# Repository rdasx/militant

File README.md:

Personal Vaporizer mod. Provides boost circuitry to run higher voltage as well as a built in USB charger. Will Probably be abandoned.

Files with "simple" in the name represent a subproject for a smaller, simpler, board that does away with the boost circuitry. Includes "in-situ" charging and a power mosfet for long switch life.

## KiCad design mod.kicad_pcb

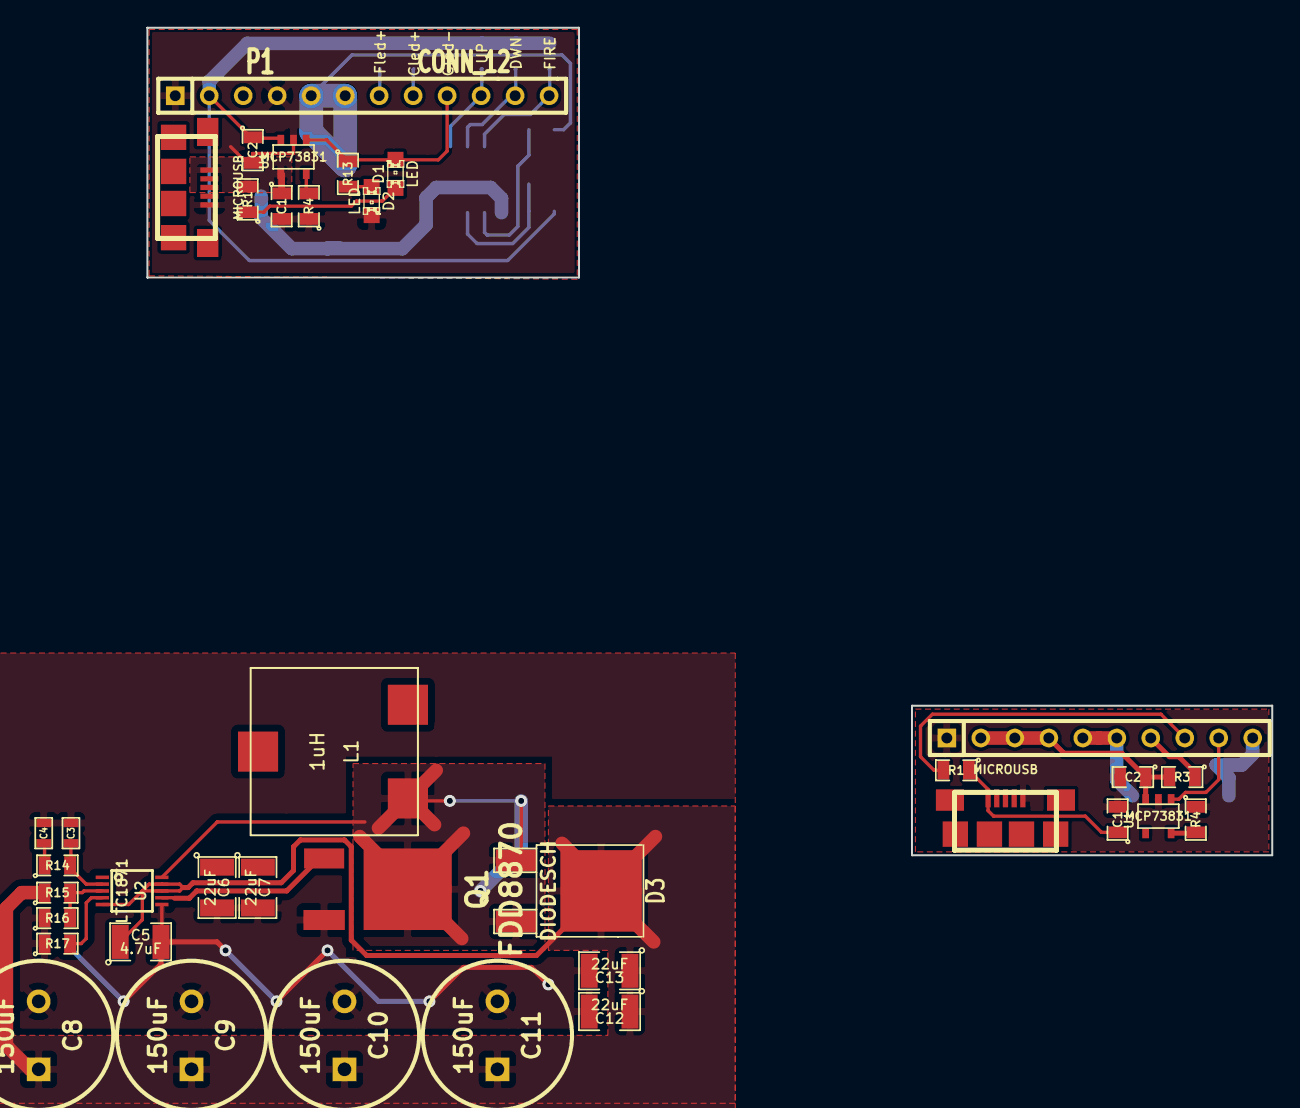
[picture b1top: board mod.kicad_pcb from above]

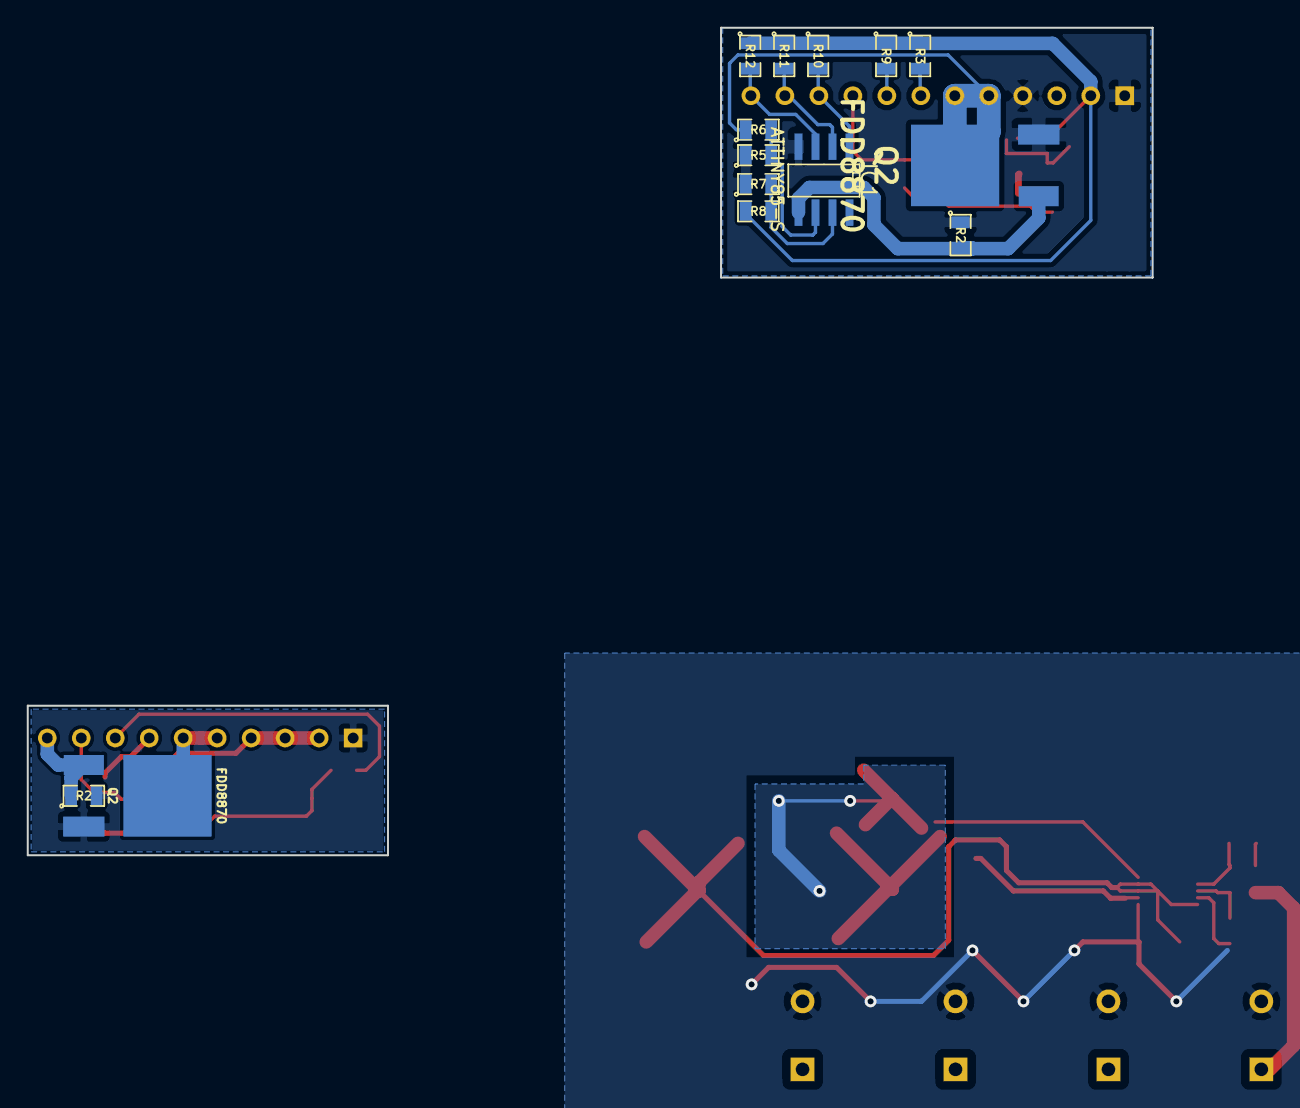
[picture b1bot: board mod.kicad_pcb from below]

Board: 2 copper layers, 51 parts (14 on the bottom side), 28 nets.

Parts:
C1, C1#2, C2, C2#2: 4.7uF; SM0805
C3: 47pF; SM0603
C4: 6800pF; SM0603
C5: 4.7uF; SM1210
C6, C7, C12, C13: 22uF; SM1210
C8, C9, C10, C11: 150uF; C2V10
D1, D2: LED; LED-0805
D3: DIODESCH; DPAK2_Schottky
IC1: ATTINY85-S; SO8(N)_MAXIC
J1, J1#2: MICROUSB; USBmicro
L1: 1uH; CEP125
P1: CONN_12; SIL-12
P1#2: CONN_10; SIL-10
Q1, Q2, Q2#2: FDD8870; TO-252_Mosfet
R1, R13: 1K; SM0805
R1#2, R3, R3#2, R5, R6, R7, R8, R9, R10, R11, R12: 330; SM0805
R2, R2#2: 10K; SM0805
R4, R4#2: 2K; SM0805
R14: 22K; SM0805
R15: 47K; SM0805
R16: 12.1K; SM0805
R17: 80.6K; SM0805
U1, U1#2: MCP73831; SOT23-5
U2: LTC1871; MSOP10-0.5

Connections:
/Atomizer+: C2#2.1, P1#2.2, P1#2.3, P1#2.4, R3#2.2, U1#2.3
/Atomizer-: P1.5, P1.6, P1#2.5, P1#2.6, Q2.D, Q2#2.D, R6.1
/Boost/Vout: C5.1, C8.1, C9.1, C10.1, C11.1, C12.1, C13.1, D3.2, P1.3, R15.1, U2.5, U2.8, U2.9
/ChargeLED+: P1.8, R9.2
/DWN-MCU: IC1.2, P1.11, R11.2
/FIRE-MCU: IC1.3, P1.12, R12.2
/FireLED+: P1.7, P1#2.7, R3.2, R3#2.1
/MCP73831 Charger/ChargeLED-: D1.2, P1.9, R13.1, U1.1
/MCP73831 Charger/Vbat: C2.1, C6.1, C7.1, IC1.8, L1.1, P1.2, R3.1, R8.2, R9.1, R10.1, R11.1, R12.1, U1.3, U2.1
/MCP73831 Charger/Vcharge: C1.1, J1.1, R1.2, U1.4
/Switch-: P1#2.10, Q2#2.G, R2#2.1
/UP-MCU: IC1.1, P1.10, R10.2
/chgLED+: P1#2.8, R1#2.2
/chgLED-: P1#2.9, U1#2.1
GND: C1.2, C1#2.2, C2.2, C2#2.2, C3.2, C4.2, C5.2, C6.2, C7.2, C8.2, C9.2, C10.2, C11.2, C12.2, C13.2, D2.2, IC1.4, J1.5, J1#2.5, P1.1, P1.4, P1#2.1, Q1.S, Q2.S, Q2#2.S, R2.1, R2#2.2, R4.1, R4#2.1, R5.1, R7.1, R16.1, R17.1, U1.2, U1#2.2, U2.6
unnamed: IC1.5, Q2.G, R2.2, R4#2.2, U1#2.5
unnamed: IC1.7, R7.2, R8.1
unnamed: IC1.6, R5.2, R6.2
unnamed: C1#2.1, J1#2.1, R1#2.1, U1#2.4
unnamed: D3.1, L1.2, Q1.D, U2.10
unnamed: Q1.G, U2.7
unnamed: R17.2, U2.4
unnamed: C4.1, R14.1
unnamed: R15.2, R16.2, U2.3
unnamed: C3.1, R14.2, U2.2
unnamed: D2.1, R13.2
unnamed: R4.2, U1.5
unnamed: D1.1, R1.1

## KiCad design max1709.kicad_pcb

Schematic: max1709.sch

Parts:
C1, C2, C4: 0.1uF; SM0805
C3: .22uF; SM0805
C5, C6, C7, C8: 150uF; C2V10
D1: DIODESCH; DPAK2
L1: 1uH
P1: CONN_6
R1: 2K; SM0805
RV1: POT
U1: MAX1709; tssop-28

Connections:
/FB: P1.3, RV1.2, U1.16
/ONA: P1.6, U1.1
/ONB: C1.1, P1.5, U1.28
/Vin: C7.1, C8.1, L1.1, P1.1
/Vout: C5.1, C6.1, D1.2 (K), P1.2, R1.2, RV1.1
GND: C1.2, C2.2, C3.2, C4.2, C5.2, C6.2, C7.2, C8.2, P1.4, RV1.3, U1.11, U1.18, U1.26
unnamed: C2.1, U1.12
unnamed: C4.1, R1.1, U1.15, U1.27
unnamed: C3.1, U1.13
unnamed: D1.1 (A), L1.2, U1.2

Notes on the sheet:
ONA ONB State 0 0 1 0 1 0 1 0 1 1 1 1
If MCU runs on Vout: Connect ONB to 270K pullup (to Vin), grounded push switch, and GPIO pin. Connect ONA to 270K pulldown (to GND), and GPIO Pin. Switch pushed, switch pulls ONB Down (REG ON), MCU Sees button push once running, MCU Pulls ONA High (REG locked ON), switch released, Switch pushed, MC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
If MCU does not run on Vout: Connect ONB to 270K pullup (to Vin) and grounded push switch or GPIO pin. Connect ONA to GND. Push switch or pull GPIO Pin low to enable (REG ON) Release switch or pull GPIO pin high to disable (REG OFF)
Vout = 1.24*(1+(R1/R2)) Where R1 is the Series Resistor and R2 is the pulldown

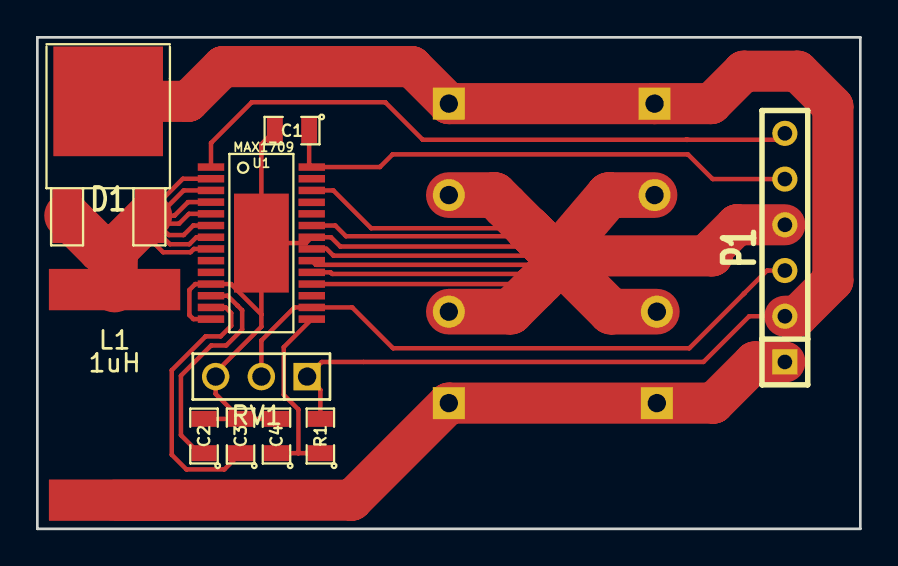
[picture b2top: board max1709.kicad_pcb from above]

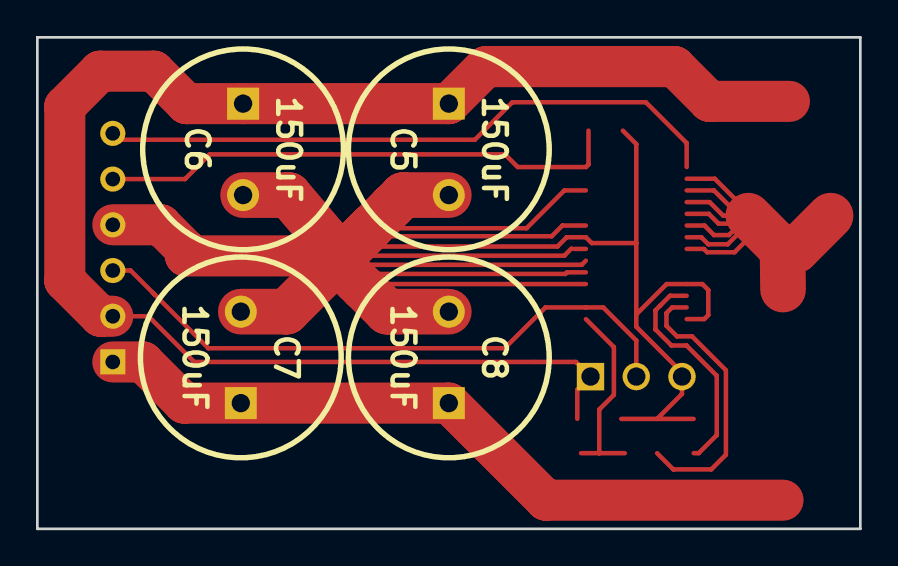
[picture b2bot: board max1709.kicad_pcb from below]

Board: 2 copper layers, 45.7 x 27.3 mm, 14 parts (4 on the bottom side), 10 nets.

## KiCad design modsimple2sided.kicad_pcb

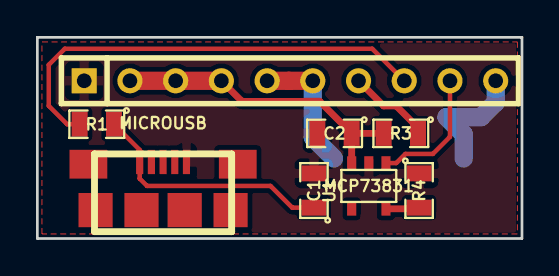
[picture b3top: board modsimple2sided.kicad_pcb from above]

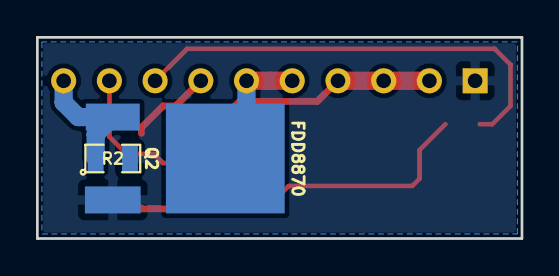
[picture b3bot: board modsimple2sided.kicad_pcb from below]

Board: 2 copper layers, 26.9 x 11.2 mm, 10 parts (2 on the bottom side), 9 nets.

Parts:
C1, C2: 4.7uF; SM0805
J1: MICROUSB; USBmicro
P1: CONN_10; SIL-10
Q2: FDD8870; TO-252_Mosfet
R1, R3: 330; SM0805
R2: 10K; SM0805
R4: 2K; SM0805
U1: MCP73831; SOT23-5

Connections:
/Atomizer+: C2.1, P1.2, P1.3, P1.4, R3.2, U1.3
/Atomizer-: P1.5, P1.6, Q2.D
/FireLED+: P1.7, R3.1
/Switch-: P1.10, Q2.G, R2.1
/chgLED+: P1.8, R1.2
/chgLED-: P1.9, U1.1
GND: C1.2, C2.2, J1.5, P1.1, Q2.S, R2.2, R4.1, U1.2
unnamed: R4.2, U1.5
unnamed: C1.1, J1.1, R1.1, U1.4

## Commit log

2013-02-26 one more
2013-02-26 modified: mod.lib modified: mod.sch
2013-03-08 modified: mod-cache.lib modified: mod.bak new file: mod.mod renamed: mod.bak -> mod.sch new file: modsimple.brd new file: modsimple.net new file: modsimple.pro new file: modsimple.sch
2013-03-12 cleanup
2013-03-12 more cleanup
2013-03-13 increased track width
2013-03-16 Licensed under TAPR OHL
2013-03-23 Added two sided board
2013-03-24 getting ready to version
2013-03-25 Switched to MAX1811
2013-03-26 moved to MCP73831
2013-03-28 part selection changes (again)
2013-03-29 finished boost schematic
2013-03-29 added TODO
2013-03-29 progress on booster circuit
2013-03-30 progress on layout
2013-03-31 many changes. Most not stable. Check TODO
2013-03-31 Changed TODO to .md
2013-03-31 formatted
2013-04-01 morning updates
2013-04-02 small tweaks
2013-04-03 writing these statements gets old
2013-04-04 Main sheet integration progress
2013-04-06 adsf
2013-04-06 started work on alternate board noname
2013-04-07 Another boost circuit, alpha ready
2013-04-08 asdf
